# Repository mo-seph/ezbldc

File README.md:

# ezbldc

A four-channel driver board for small gimbal-type brushless motors: a
Seeed XIAO ESP32-S3 Plus, four TI DRV8313 three-phase drivers, four encoder
ports, I2C in and out on Qwiic connectors, one 12 V supply. 80 × 62 mm,
four layers, designed in KiCad 10 for assembly at JLCPCB.

## Status

Revision **v0.4**. The design passes KiCad's electrical and design rule
checks, the board matches the schematic, and the design and fabrication
files have been through three review rounds. **No test results on real
hardware are recorded here yet: treat it as an unproven design.** The
things most likely to need attention are under [Things to know](#things-to-know).

## What is on it

- **Four motor channels.** Each is a DRV8313 wired as TI's reference
  circuit, with its own 1.1 A-hold polyfuse, 100 µF bulk capacitor and a
  red fault LED. Phase traces are 0.65 mm (about 1.7 A for a 10 °C rise).
  Motors plug onto plain 1 × 3, 2.54 mm headers.
- **Three PWM inputs per channel** from the XIAO (twelve in all, which is
  exactly what the ESP32-S3's two motor-control PWM units provide). There
  is no current sensing: the board is driven in voltage mode.
- **One shared enable line** on the drivers' reset pins, pulled low, so
  the outputs are off through boot, reset and flashing, and a low pulse
  clears a latched fault.
- **Four encoder ports** (JST-XH, 5 pin) beside the motor headers: a
  shared clock and data line and one chip select each, from a 74HC139.
- **I2C** on two Qwiic connectors (in and out). Pull-ups are not fitted.
- **Power**: 12 V on a 5.5 mm barrel jack (2.0 mm pin), centre positive,
  with a second jack wired straight through for the next board. Reverse-polarity
  diode, 15 V TVS clamp, and a 7805 making 5 V for the XIAO.
- A WS2812B status LED and fourteen test pads.

## Pin map

| Function | XIAO pad | GPIO |
|---|---|---|
| Motor 1 IN1 / IN2 / IN3 | D9 / D17 / D10 | 8 / 13 / 9 |
| Motor 2 IN1 / IN2 / IN3 | D19 / D8 / D18 | 11 / 7 / 12 |
| Motor 3 IN1 / IN2 / IN3 | D12 / D2 / D13 | 39 / 3 / 40 |
| Motor 4 IN1 / IN2 / IN3 | D0 / D11 / D1 | 1 / 38 / 2 |
| Driver enable (high = on) | D3 | 4 |
| Encoder clock | D14 | 41 |
| Encoder data | D15 | 42 |
| Encoder select A0 / A1 | D6 / D7 | 43 / 44 |
| Status LED data | D16 | 10 |
| I2C SDA / SCL | D4 / D5 | 5 / 6 |

D11–D19 are the XIAO Plus's extra pads, the small ones between its
fourteen main edge pads. `kicad/design_spec.py` is the authority for this
table.

## Connectors

- **Motor headers J11–J14**: pin 1 (phase 1) is the one nearest the
  middle of the board, pin 3 is at the board edge.
- **Encoder sockets J21–J24**: pin 1 is at the board edge.
  1 = 3V3, 2 = GND, 3 = clock, 4 = data, 5 = chip select (active low).
  Select lines A1 A0 = 00, 01, 10, 11 pick encoder 1, 2, 3, 4. One select
  is always low.
- **Qwiic J3 (in), J4 (out)**: 1 = GND, 2 = 3V3, 3 = SDA, 4 = SCL. The 3V3
  wire only passes from one connector to the other; closing jumper JP1
  joins it to the board's own 3.3 V.
- **J1 / J2**: 12 V in and out, centre positive.

The board itself carries no part designators (it is too dense).
[`kicad/output/assembly_top.pdf`](kicad/output/assembly_top.pdf) is the map
of which part is where.

## Encoder options

The port was designed for MagnTek MT6701 encoders read over SSI. What it
supports:

- **No encoder**: run a channel open loop.
- **One MT6701 on SSI**: fine, in any socket.
- **Several MT6701 on SSI: unproven.** With its chip select high an
  MT6701 becomes an I2C slave on the same clock and data pins, and its
  datasheet does not say the data pin is released. It may well work at an
  SSI clock of about 1 MHz or less; it has not been tested. If it does
  not, a tri-state buffer in the data line at each encoder, enabled by
  that encoder's chip select, fixes it without changing this board.
- **Other SPI-type encoders**: any part whose data output goes
  high-impedance while its chip select is high, and which can be read
  without a MOSI line (the port has none).
- **I2C encoders on the same two pins**, as a firmware choice: data is
  SDA (it has a 10 k pull-up and 100 Ω in series), clock is SCL. The
  clock line has **no pull-up on this board**, so the encoder boards must
  bring one. Leave pin 5 unwired. The encoders need distinct addresses.

## Things to know

- **Sustained current.** The input diode D1 is the warmest part of the
  supply path. About 3 A for the whole board is the comfortable sustained
  figure; the jacks are rated 5 A.
- **7805 heat.** About 0.7 W with the XIAO's radio off, about 1.25 W with
  WiFi on, which wants a heatsink. A K7805-500R3 switching module fits
  the same three holes. The silkscreen shows which side the tab goes:
  fitted backwards, the regulator puts about 11 V on the XIAO's 5 V pin.
- **The XIAO is soldered on by hand**, flat on its pads. JLCPCB do not
  stock it.
- **The status LED runs from 3.3 V**, below that part's rated 3.5 V.
- **Fault outputs light LEDs only.** The microcontroller cannot read
  them: all its pins are used.
- **Ten logic nets are autorouted.** They pass the rule checks but are
  not tidy. Power, the motor phases, the buses and the I2C lines are
  routed by hand (in `kicad/tools/build_board.py`).
- SDA, SCL and the Qwiic 3V3 wire cross the board on inner layer 2,
  through the 3.3 V plane.

## What is in this repository

| Path | What |
|---|---|
| `kicad/bldc_driver_board.kicad_pro` | The KiCad 10 project: two-page schematic and the routed board |
| `kicad/lib/` | The custom symbols and footprints (XIAO Plus, barrel jack, regulator) and their generators |
| `kicad/output/schematic.pdf` | The schematic |
| `kicad/output/assembly_top.pdf` | Part positions, with pin 1 marked |
| `kicad/output/signal_map.png` | The copper, coloured by kind of signal |
| `kicad/output/bldc_driver_board.step` | 3D model |
| `kicad/output/fab/` | Gerbers and drill files (zipped and loose), JLCPCB placement file and BOMs |
| `BOM.md`, `bom_jlcpcb.csv` | Parts with LCSC numbers, and an assembly cost estimate |
| `kicad/design_spec.py` | Every part and net, as data. The schematic and board are generated from it |
| `kicad/gen_schematic.py`, `kicad/tools/` | The generators (see below) |

## Ordering from JLCPCB

1. Upload `kicad/output/fab/bldc_driver_board_gerbers.zip`. It should be
   detected as 4 layers, 80 × 62.05 mm. Inner layer 1 is the solid ground
   plane.
2. Choose a lead-free HASL or ENIG finish rather than the default OSP:
   the XIAO and any hand-fitted parts are soldered after the board has
   been through the oven. State the layer order in the remark field:
   F_Cu, In1_Cu (`.g1`), In2_Cu (`.g2`), B_Cu.
3. Assembly: top side. Upload `bom_jlcpcb.csv` (or
   `bom_jlcpcb_smd_only.csv` to fit the through-hole parts yourself) and
   `cpl_jlcpcb.csv`.
4. **Check the placement preview** against `assembly_top.pdf` before
   paying: the + of the five round capacitors, pin 1 of the five ICs, the
   cathode stripe of the three diodes and four fault LEDs, the status LED,
   and that the Qwiic sockets face outward. The rotations in the
   placement file were worked out part by part from JLCPCB's own
   footprints, but their preview is the final word.

## Regenerating the design

The schematic and the board are generated, not drawn:

- `python3 kicad/gen_schematic.py` writes the schematic from
  `design_spec.py` (`check` runs ERC and compares the netlist with the
  spec; `export` writes the PDF).
- `kicad/tools/build_board.py`, run with KiCad's own Python, builds the
  board: placement, all hand-designed copper, planes, silkscreen.
- `kicad/tools/autoroute.py` has Freerouting place the remaining logic
  nets and runs the design rule check.
- `kicad/tools/export_outputs.py` rewrites everything in `kicad/output/`.

**`build_board.py` and `autoroute.py` overwrite the board file.** Anything
edited by hand in KiCad is lost if they are run again, and the autorouter
gives a different result each time.

They were written for KiCad 10 on macOS and have paths to match. The
autorouter step also needs Freerouting 2.1.0 (Java 21) and, for the
Specctra export and import, a local install of the KiCad MCP server that
`kicad/tools/kicad_cmd.py` calls; adapt that file to your own setup.
`export_outputs.py` needs `rsvg-convert`.

A few comments and schematic notes mention a "Node" board and a
"Central". These are other boards in the system this one was built for:
an earlier I2C peripheral board whose outline, mounting holes and
connector positions this board copies, and the I2C bus controller.

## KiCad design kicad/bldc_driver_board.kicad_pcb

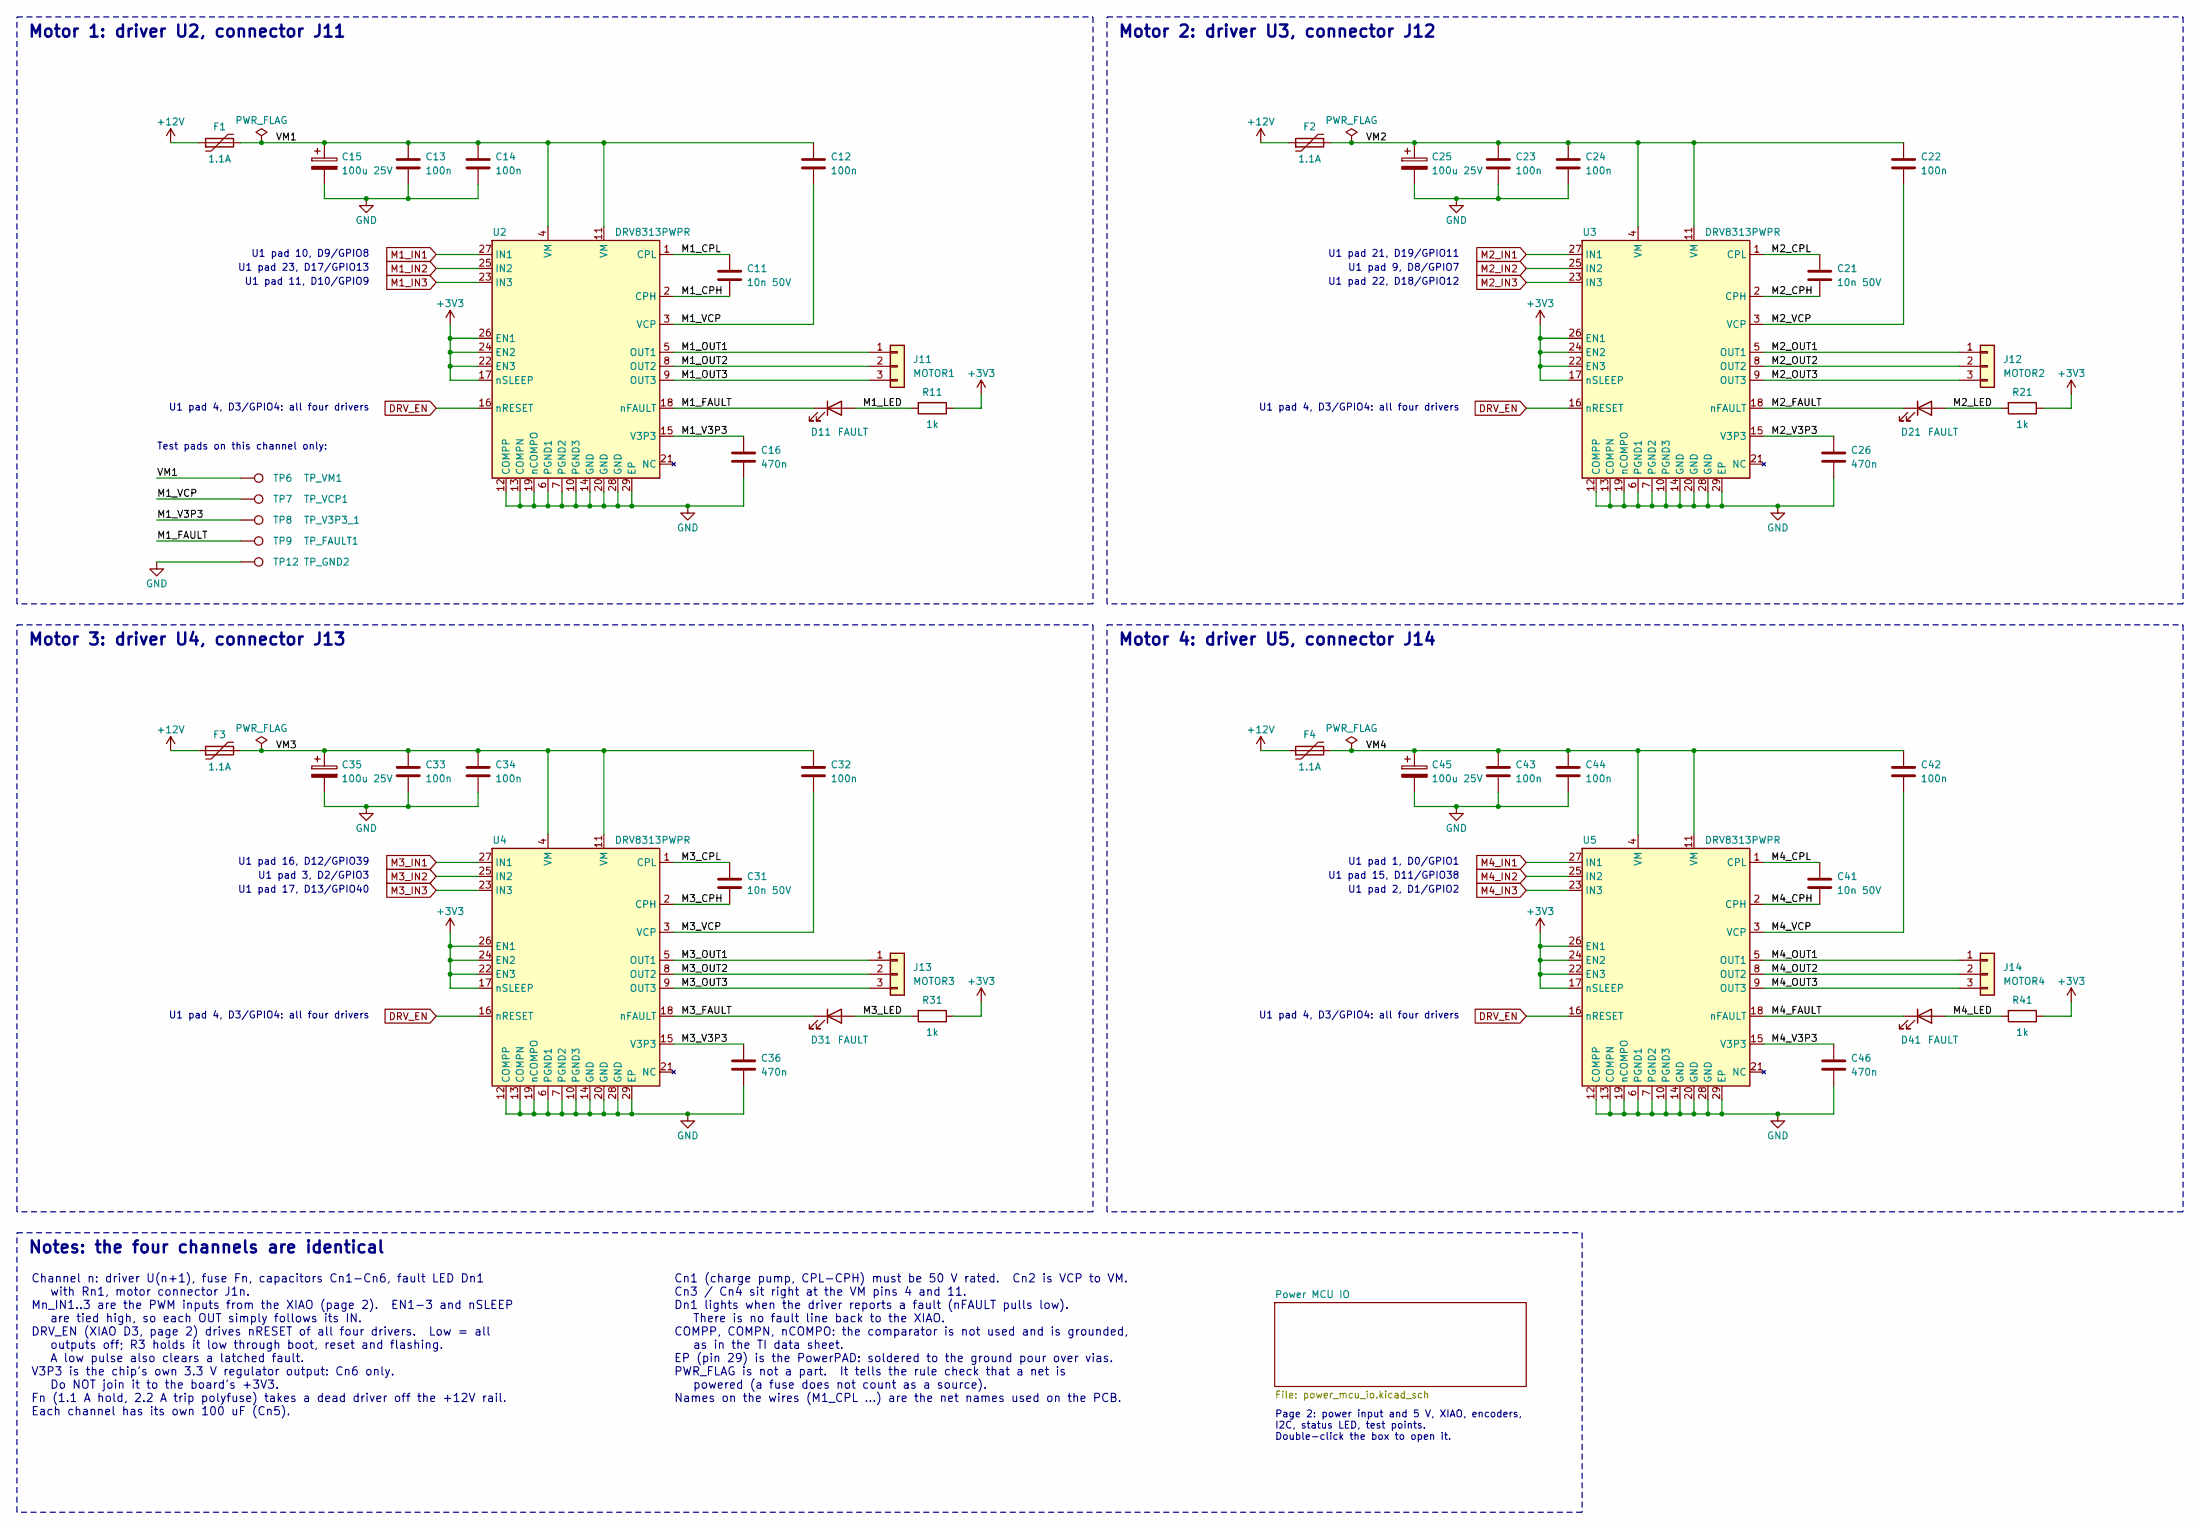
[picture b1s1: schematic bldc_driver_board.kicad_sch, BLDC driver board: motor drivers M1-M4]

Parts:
C11, C21, C31, C41: 10n 50V; C_0805_2012Metric; LCSC C1710
C12, C13, C14, C22, C23, C24, C32, C33, C34, C42, C43, C44: 100n; C_0805_2012Metric; LCSC C49678
C15, C25, C35, C45: 100u 25V; CP_Elec_6.3x7.7; LCSC C2836443
C16, C26, C36, C46: 470n; C_0805_2012Metric; LCSC C13967
D11, D21, D31, D41: FAULT; LED_0805_2012Metric; LCSC C84256
F1, F2, F3, F4: 1.1A; Fuse_1812_4532Metric; LCSC C21000
J11: MOTOR1; PinHeader_1x03_P2.54mm_Vertical; LCSC C2937625
J12: MOTOR2; PinHeader_1x03_P2.54mm_Vertical; LCSC C2937625
J13: MOTOR3; PinHeader_1x03_P2.54mm_Vertical; LCSC C2937625
J14: MOTOR4; PinHeader_1x03_P2.54mm_Vertical; LCSC C2937625
R11, R21, R31, R41: 1k; R_0805_2012Metric; LCSC C17513
TP6: TP_VM1; TestPoint_Pad_D1.5mm
TP7: TP_VCP1; TestPoint_Pad_D1.5mm
TP8: TP_V3P3_1; TestPoint_Pad_D1.5mm
TP9: TP_FAULT1; TestPoint_Pad_D1.5mm
TP12: TP_GND2; TestPoint_Pad_D1.5mm
U2, U3, U4, U5: DRV8313PWPR; HTSSOP-28-1EP_4.4x9.7mm_P0.65mm_EP2.85x5.4mm_ThermalVias; LCSC C92482

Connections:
+3V3: R11.1, R21.1, R31.1, R41.1, U2.17 (nSLEEP), U2.22 (EN3), U2.24 (EN2), U2.26 (EN1), U3.17 (nSLEEP), U3.22 (EN3), U3.24 (EN2), U3.26 (EN1), U4.17 (nSLEEP), U4.22 (EN3), U4.24 (EN2), U4.26 (EN1), U5.17 (nSLEEP), U5.22 (EN3), U5.24 (EN2), U5.26 (EN1); also elsewhere on the board
+12V: F1.1, F2.1, F3.1, F4.1; also elsewhere on the board
/M1_CPH: C11.2, U2.2 (CPH)
/M1_CPL: C11.1, U2.1 (CPL)
/M1_FAULT: D11.1 (K), TP9.1, U2.18 (nFAULT)
/M1_LED: D11.2 (A), R11.2
/M1_OUT1: J11.1, U2.5 (OUT1)
/M1_OUT2: J11.2, U2.8 (OUT2)
/M1_OUT3: J11.3, U2.9 (OUT3)
/M1_V3P3: C16.1, TP8.1, U2.15 (V3P3)
/M1_VCP: C12.1, TP7.1, U2.3 (VCP)
/M2_CPH: C21.2, U3.2 (CPH)
/M2_CPL: C21.1, U3.1 (CPL)
/M2_FAULT: D21.1 (K), U3.18 (nFAULT)
/M2_LED: D21.2 (A), R21.2
/M2_OUT1: J12.1, U3.5 (OUT1)
/M2_OUT2: J12.2, U3.8 (OUT2)
/M2_OUT3: J12.3, U3.9 (OUT3)
/M2_V3P3: C26.1, U3.15 (V3P3)
/M2_VCP: C22.1, U3.3 (VCP)
/M3_CPH: C31.2, U4.2 (CPH)
/M3_CPL: C31.1, U4.1 (CPL)
/M3_FAULT: D31.1 (K), U4.18 (nFAULT)
/M3_LED: D31.2 (A), R31.2
/M3_OUT1: J13.1, U4.5 (OUT1)
/M3_OUT2: J13.2, U4.8 (OUT2)
/M3_OUT3: J13.3, U4.9 (OUT3)
/M3_V3P3: C36.1, U4.15 (V3P3)
/M3_VCP: C32.1, U4.3 (VCP)
/M4_CPH: C41.2, U5.2 (CPH)
/M4_CPL: C41.1, U5.1 (CPL)
/M4_FAULT: D41.1 (K), U5.18 (nFAULT)
/M4_LED: D41.2 (A), R41.2
/M4_OUT1: J14.1, U5.5 (OUT1)
/M4_OUT2: J14.2, U5.8 (OUT2)
/M4_OUT3: J14.3, U5.9 (OUT3)
/M4_V3P3: C46.1, U5.15 (V3P3)
/M4_VCP: C42.1, U5.3 (VCP)
/VM1: C12.2, C13.1, C14.1, C15.1, F1.2, TP6.1, U2.4 (VM), U2.11 (VM)
/VM2: C22.2, C23.1, C24.1, C25.1, F2.2, U3.4 (VM), U3.11 (VM)
/VM3: C32.2, C33.1, C34.1, C35.1, F3.2, U4.4 (VM), U4.11 (VM)
/VM4: C42.2, C43.1, C44.1, C45.1, F4.2, U5.4 (VM), U5.11 (VM)
DRV_EN: U2.16 (nRESET), U3.16 (nRESET), U4.16 (nRESET), U5.16 (nRESET); also elsewhere on the board
GND: C13.2, C14.2, C15.2, C16.2, C23.2, C24.2, C25.2, C26.2, C33.2, C34.2, C35.2, C36.2, C43.2, C44.2, C45.2, C46.2, TP12.1, U2.6 (PGND1), U2.7 (PGND2), U2.10 (PGND3), U2.12 (COMPP), U2.13 (COMPN), U2.14 (GND), U2.19 (nCOMPO), U2.20 (GND), U2.28 (GND), U2.29 (EP), U3.6 (PGND1), U3.7 (PGND2), U3.10 (PGND3), U3.12 (COMPP), U3.13 (COMPN), U3.14 (GND), U3.19 (nCOMPO), U3.20 (GND), U3.28 (GND), U3.29 (EP), U4.6 (PGND1), U4.7 (PGND2), U4.10 (PGND3), U4.12 (COMPP), U4.13 (COMPN), U4.14 (GND), U4.19 (nCOMPO), U4.20 (GND), U4.28 (GND), U4.29 (EP), U5.6 (PGND1), U5.7 (PGND2), U5.10 (PGND3), U5.12 (COMPP), U5.13 (COMPN), U5.14 (GND), U5.19 (nCOMPO), U5.20 (GND), U5.28 (GND), U5.29 (EP); also elsewhere on the board
M1_IN1: U2.27 (IN1); also elsewhere on the board
M1_IN2: U2.25 (IN2); also elsewhere on the board
M1_IN3: U2.23 (IN3); also elsewhere on the board
M2_IN1: U3.27 (IN1); also elsewhere on the board
M2_IN2: U3.25 (IN2); also elsewhere on the board
M2_IN3: U3.23 (IN3); also elsewhere on the board
M3_IN1: U4.27 (IN1); also elsewhere on the board
M3_IN2: U4.25 (IN2); also elsewhere on the board
M3_IN3: U4.23 (IN3); also elsewhere on the board
M4_IN1: U5.27 (IN1); also elsewhere on the board
M4_IN2: U5.25 (IN2); also elsewhere on the board
M4_IN3: U5.23 (IN3); also elsewhere on the board

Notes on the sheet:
Motor 1: driver U2, connector J11
U1 pad 10, D9/GPIO8
U1 pad 23, D17/GPIO13
U1 pad 11, D10/GPIO9
U1 pad 4, D3/GPIO4: all four drivers
Test pads on this channel only:
Motor 2: driver U3, connector J12
U1 pad 21, D19/GPIO11
U1 pad 9, D8/GPIO7
U1 pad 22, D18/GPIO12
Motor 3: driver U4, connector J13
U1 pad 16, D12/GPIO39
U1 pad 3, D2/GPIO3
U1 pad 17, D13/GPIO40
Motor 4: driver U5, connector J14
U1 pad 1, D0/GPIO1
U1 pad 15, D11/GPIO38
U1 pad 2, D1/GPIO2
Notes: the four channels are identical
Channel n: driver U(n+1), fuse Fn, capacitors Cn1-Cn6, fault LED Dn1 with Rn1, motor connector J1n. Mn_IN1..3 are the PWM inputs from the XIAO (page 2). EN1-3 and nSLEEP are tied high, so each OUT simply follows its IN. DRV_EN (XIAO D3, page 2) drives nRESET of all four drivers. Low = all outputs o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
Cn1 (charge pump, CPL-CPH) must be 50 V rated. Cn2 is VCP to VM. Cn3 / Cn4 sit right at the VM pins 4 and 11. Dn1 lights when the driver reports a fault (nFAULT pulls low). There is no fault line back to the XIAO. COMPP, COMPN, nCOMPO: the comparator is not used and is grounded, as in the TI data s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
Page 2: power input and 5 V, XIAO, encoders, I2C, status LED, test points. Double-click the box to open it.

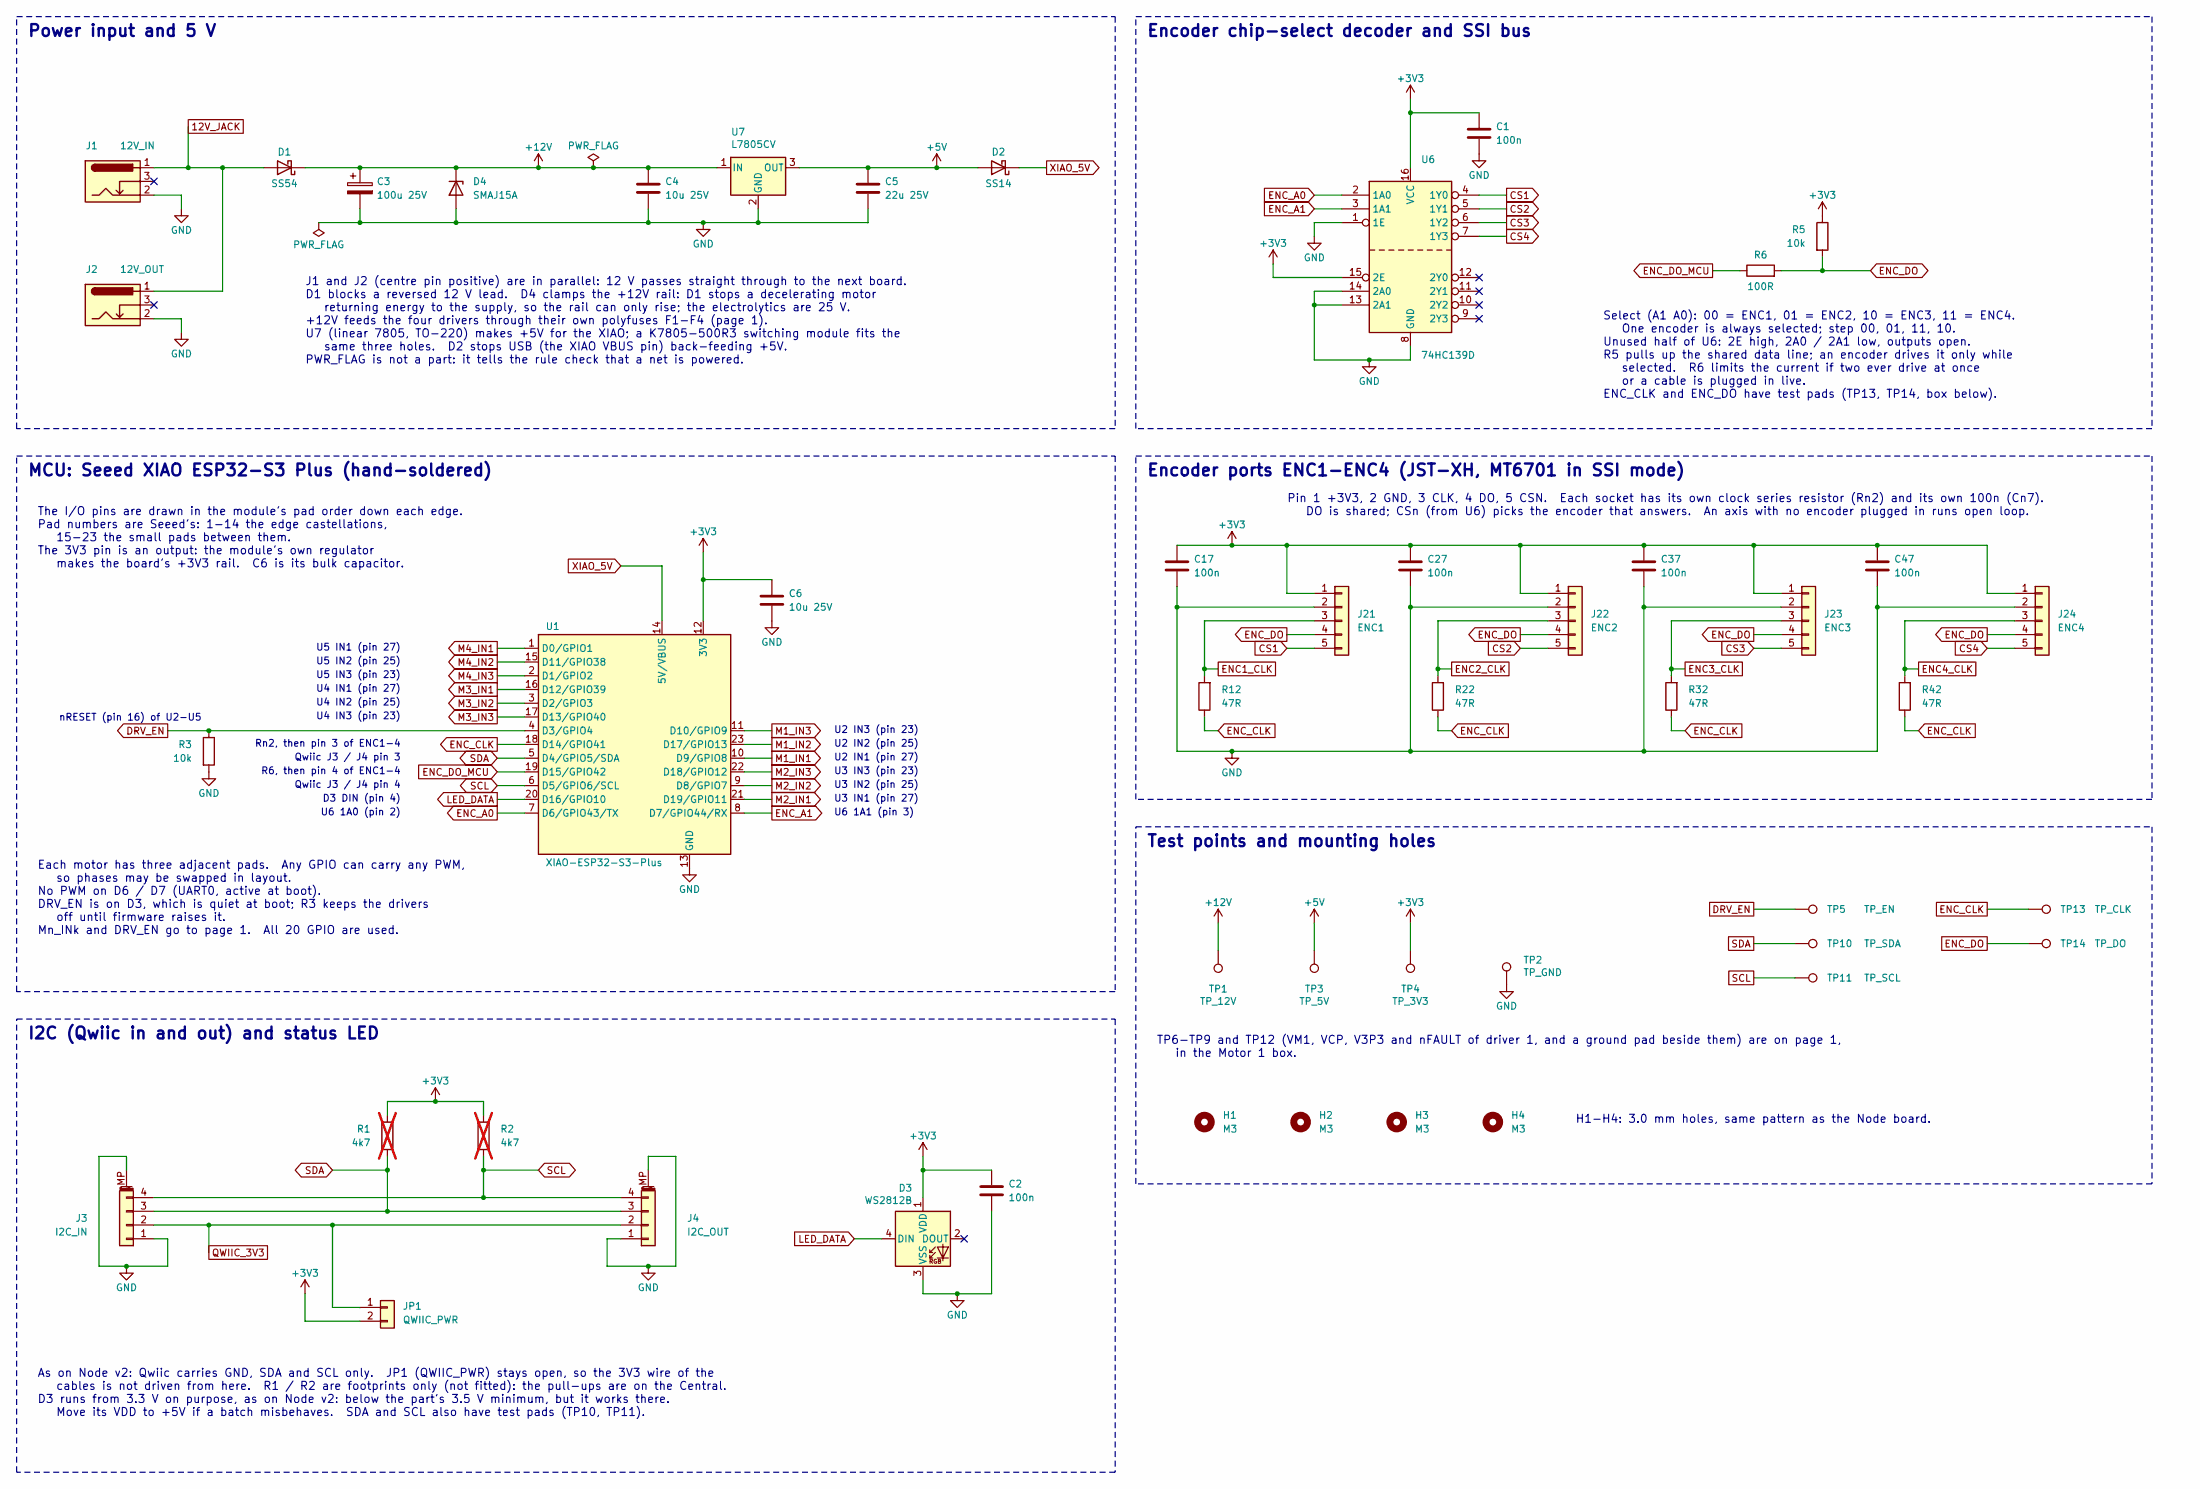
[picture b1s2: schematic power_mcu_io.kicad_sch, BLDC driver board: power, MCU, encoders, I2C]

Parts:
C1, C2: 100n; C_0805_2012Metric; LCSC C49678
C3: 100u 25V; CP_Elec_6.3x7.7; LCSC C2836443
C4, C6: 10u 25V; C_0805_2012Metric; LCSC C15850
C5: 22u 25V; C_0805_2012Metric; LCSC C45783
C17, C27, C37, C47: 100n; C_0603_1608Metric; LCSC C14663
D1: SS54; D_SMA; LCSC C22452
D2: SS14; D_SMA; LCSC C2480
D3: WS2812B; LED_WS2812B_PLCC4_5.0x5.0mm_P3.2mm; LCSC C2843785
D4: SMAJ15A; D_SMA; LCSC C86819
H1, H2, H3, H4: M3; MountingHole_3mm
J1: 12V_IN; XKB_DC-005-5A-2.0; LCSC C381116
J2: 12V_OUT; XKB_DC-005-5A-2.0; LCSC C381116
J3: I2C_IN; JST_SH_SM04B-SRSS-TB_1x04-1MP_P1.00mm_Horizontal; LCSC C160404
J4: I2C_OUT; JST_SH_SM04B-SRSS-TB_1x04-1MP_P1.00mm_Horizontal; LCSC C160404
J21: ENC1; JST_XH_B5B-XH-A_1x05_P2.50mm_Vertical; LCSC C157991
J22: ENC2; JST_XH_B5B-XH-A_1x05_P2.50mm_Vertical; LCSC C157991
J23: ENC3; JST_XH_B5B-XH-A_1x05_P2.50mm_Vertical; LCSC C157991
J24: ENC4; JST_XH_B5B-XH-A_1x05_P2.50mm_Vertical; LCSC C157991
JP1: QWIIC_PWR; PinHeader_1x02_P2.54mm_Vertical; LCSC C492401
R1, R2: 4k7; R_0805_2012Metric; LCSC C17673; not fitted
R3, R5: 10k; R_0805_2012Metric; LCSC C17414
R6: 100R; R_0805_2012Metric; LCSC C17408
R12, R22, R32, R42: 47R; R_0603_1608Metric; LCSC C23182
TP1: TP_12V; TestPoint_Pad_D1.5mm
TP2: TP_GND; TestPoint_Pad_D1.5mm
TP3: TP_5V; TestPoint_Pad_D1.5mm
TP4: TP_3V3; TestPoint_Pad_D1.5mm
TP5: TP_EN; TestPoint_Pad_D1.5mm
TP10: TP_SDA; TestPoint_Pad_D1.5mm
TP11: TP_SCL; TestPoint_Pad_D1.5mm
TP13: TP_CLK; TestPoint_Pad_D1.5mm
TP14: TP_DO; TestPoint_Pad_D1.5mm
U1: XIAO-ESP32-S3-Plus; XIAO-ESP32-S3-Plus-SMD
U6: 74HC139D; SOIC-16_3.9x9.9mm_P1.27mm; LCSC C5603
U7: L7805CV; SIP-3_K7805_or_TO-220; LCSC C111887

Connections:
12V_JACK: D1.2 (A), J1.1, J2.1
+3V3: C1.1, C2.1, C6.1, C17.1, C27.1, C37.1, C47.1, D3.1 (VDD), J21.1, J22.1, J23.1, J24.1, JP1.2, R1.1, R2.1, R5.1, TP4.1, U1.12 (3V3), U6.15 (2E), U6.16 (VCC); also elsewhere on the board
+5V: C5.1, D2.2 (A), TP3.1, U7.3 (OUT)
+12V: C3.1, C4.1, D1.1 (K), D4.1 (K), TP1.1, U7.1 (IN); also elsewhere on the board
CS1: J21.5, U6.4 (1Y0)
CS2: J22.5, U6.5 (1Y1)
CS3: J23.5, U6.6 (1Y2)
CS4: J24.5, U6.7 (1Y3)
DRV_EN: R3.1, TP5.1, U1.4 (D3/GPIO4); also elsewhere on the board
ENC1_CLK: J21.3, R12.2
ENC2_CLK: J22.3, R22.2
ENC3_CLK: J23.3, R32.2
ENC4_CLK: J24.3, R42.2
ENC_A0: U1.7 (D6/GPIO43/TX), U6.2 (1A0)
ENC_A1: U1.8 (D7/GPIO44/RX), U6.3 (1A1)
ENC_CLK: R12.1, R22.1, R32.1, R42.1, TP13.1, U1.18 (D14/GPIO41)
ENC_DO: J21.4, J22.4, J23.4, J24.4, R5.2, R6.2, TP14.1
ENC_DO_MCU: R6.1, U1.19 (D15/GPIO42)
GND: C1.2, C2.2, C3.2, C4.2, C5.2, C6.2, C17.2, C27.2, C37.2, C47.2, D3.3 (VSS), D4.2 (A), J1.2, J2.2, J3.1, J3.MP (MountPin), J4.1, J4.MP (MountPin), J21.2, J22.2, J23.2, J24.2, R3.2, TP2.1, U1.13 (GND), U6.1 (1E), U6.8 (GND), U6.13 (2A1), U6.14 (2A0), U7.2 (GND); also elsewhere on the board
LED_DATA: D3.4 (DIN), U1.20 (D16/GPIO10)
M1_IN1: U1.10 (D9/GPIO8); also elsewhere on the board
M1_IN2: U1.23 (D17/GPIO13); also elsewhere on the board
M1_IN3: U1.11 (D10/GPIO9); also elsewhere on the board
M2_IN1: U1.21 (D19/GPIO11); also elsewhere on the board
M2_IN2: U1.9 (D8/GPIO7); also elsewhere on the board
M2_IN3: U1.22 (D18/GPIO12); also elsewhere on the board
M3_IN1: U1.16 (D12/GPIO39); also elsewhere on the board
M3_IN2: U1.3 (D2/GPIO3); also elsewhere on the board
M3_IN3: U1.17 (D13/GPIO40); also elsewhere on the board
M4_IN1: U1.1 (D0/GPIO1); also elsewhere on the board
M4_IN2: U1.15 (D11/GPIO38); also elsewhere on the board
M4_IN3: U1.2 (D1/GPIO2); also elsewhere on the board
QWIIC_3V3: J3.2, J4.2, JP1.1
SCL: J3.4, J4.4, R2.2, TP11.1, U1.6 (D5/GPIO6/SCL)
SDA: J3.3, J4.3, R1.2, TP10.1, U1.5 (D4/GPIO5/SDA)
XIAO_5V: D2.1 (K), U1.14 (5V/VBUS)

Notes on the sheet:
Power input and 5 V
J1 and J2 (centre pin positive) are in parallel: 12 V passes straight through to the next board. D1 blocks a reversed 12 V lead. D4 clamps the +12V rail: D1 stops a decelerating motor returning energy to the supply, so the rail can only rise; the electrolytics are 25 V. +12V feeds the four drivers 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
MCU: Seeed XIAO ESP32-S3 Plus (hand-soldered)
U5 IN1 (pin 27)
U5 IN2 (pin 25)
U5 IN3 (pin 23)
U4 IN1 (pin 27)
U4 IN2 (pin 25)
U4 IN3 (pin 23)
Rn2, then pin 3 of ENC1-4
Qwiic J3 / J4 pin 3
R6, then pin 4 of ENC1-4
Qwiic J3 / J4 pin 4
D3 DIN (pin 4)
U6 1A0 (pin 2)
U2 IN3 (pin 23)
U2 IN2 (pin 25)
U2 IN1 (pin 27)
U3 IN3 (pin 23)
U3 IN2 (pin 25)
U3 IN1 (pin 27)
U6 1A1 (pin 3)
nRESET (pin 16) of U2-U5
The I/O pins are drawn in the module's pad order down each edge. Pad numbers are Seeed's: 1-14 the edge castellations, 15-23 the small pads between them. The 3V3 pin is an output: the module's own regulator makes the board's +3V3 rail. C6 is its bulk capacitor.
Each motor has three adjacent pads. Any GPIO can carry any PWM, so phases may be swapped in layout. No PWM on D6 / D7 (UART0, active at boot). DRV_EN is on D3, which is quiet at boot; R3 keeps the drivers off until firmware raises it. Mn_INk and DRV_EN go to page 1. All 20 GPIO are used.
I2C (Qwiic in and out) and status LED
As on Node v2: Qwiic carries GND, SDA and SCL only. JP1 (QWIIC_PWR) stays open, so the 3V3 wire of the cables is not driven from here. R1 / R2 are footprints only (not fitted): the pull-ups are on the Central. D3 runs from 3.3 V on purpose, as on Node v2: below the part's 3.5 V minimum, but it work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
Encoder chip-select decoder and SSI bus
Select (A1 A0): 00 = ENC1, 01 = ENC2, 10 = ENC3, 11 = ENC4. One encoder is always selected; step 00, 01, 11, 10. Unused half of U6: 2E high, 2A0 / 2A1 low, outputs open. R5 pulls up the shared data line; an encoder drives it only while selected. R6 limits the current if two ever drive at once or a 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
Encoder ports ENC1-ENC4 (JST-XH, MT6701 in SSI mode)
Pin 1 +3V3, 2 GND, 3 CLK, 4 DO, 5 CSN. Each socket has its own clock series resistor (Rn2) and its own 100n (Cn7). DO is shared; CSn (from U6) picks the encoder that answers. An axis with no encoder plugged in runs open loop.
Test points and mounting holes
TP6-TP9 and TP12 (VM1, VCP, V3P3 and nFAULT of driver 1, and a ground pad beside them) are on page 1, in the Motor 1 box.
H1-H4: 3.0 mm holes, same pattern as the Node board.

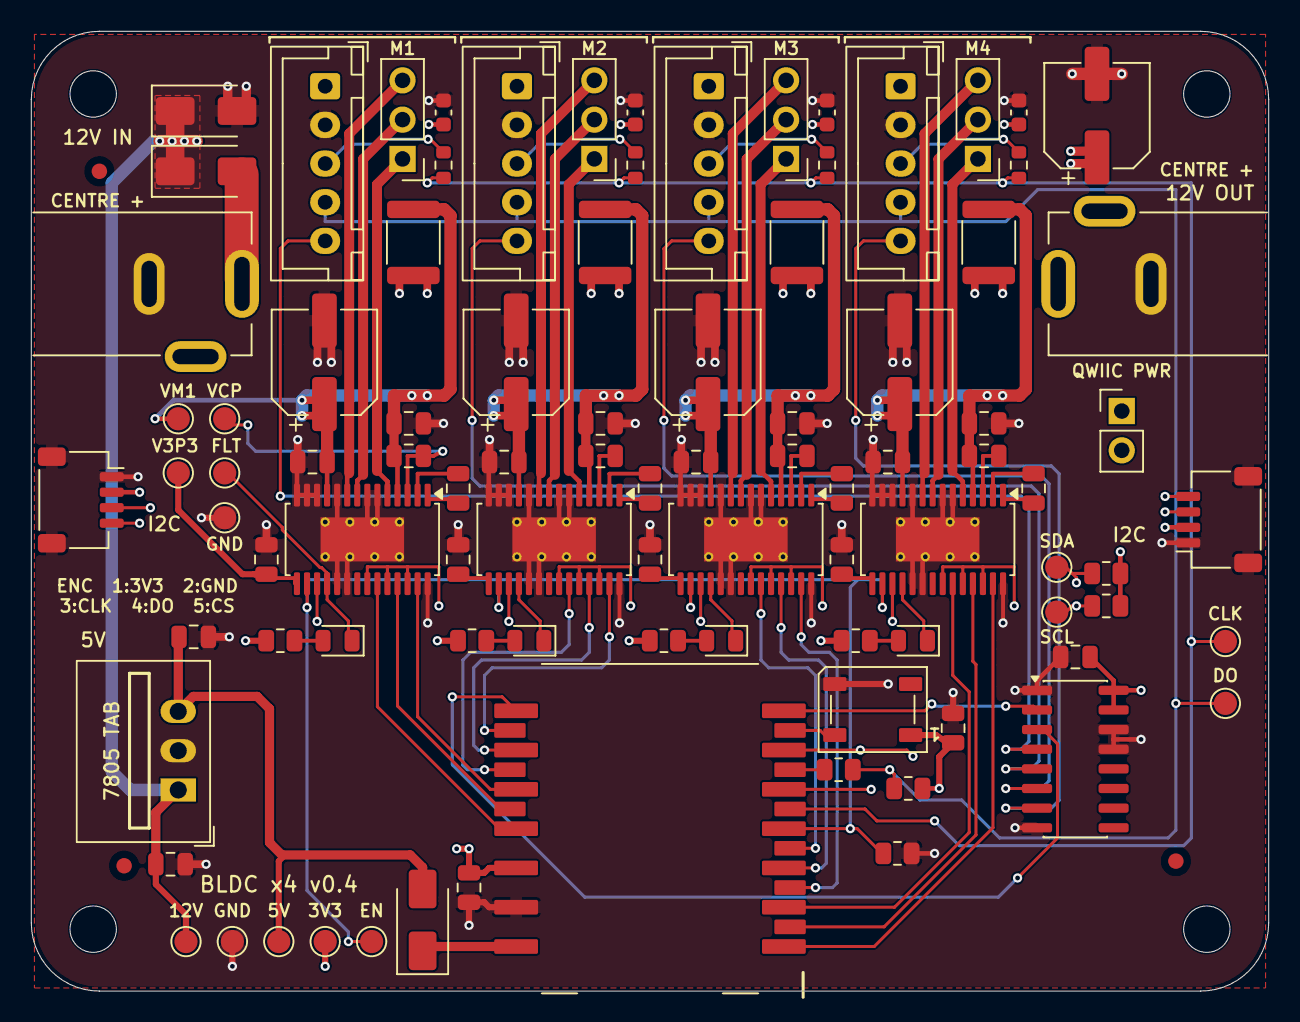
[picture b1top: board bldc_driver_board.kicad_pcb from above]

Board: 4 copper layers, 80.0 x 62.1 mm, 100 parts (0 on the bottom side), 76 nets.

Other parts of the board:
FID1, FID2, FID3: Fiducial; Fiducial_1mm_Mask2mm

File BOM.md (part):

# 4-channel BLDC driver board — BOM (per board)

Parts were checked against JLCPCB's live catalogue on 2026-11-10 and
2026-11-11 (part number, package, basic / extended, stock). Prices are
JLCPCB's quantity-1 tier in USD on those days. `bom_jlcpcb.csv` is the
same list in JLCPCB's upload format;
`kicad/output/fab/bom_jlcpcb_smd_only.csv` is the surface-mount half, for
an order where the through-hole parts are fitted by hand. Designators
match the KiCad project.

## Surface mount (JLCPCB assembles these)

| Designators | Qty | Part | Package | LCSC | JLCPCB | $ each |
|---|---|---|---|---|---|---|
| U2, U3, U4, U5 | 4 | DRV8313PWPR (TI) | HTSSOP-28, PowerPAD | C92482 | extended | 4.47 |
| U6 | 1 | 74HC139D,653 (Nexperia) | SOIC-16 | C5603 | extended | 0.25 |
| C12 C13 C14, C22 C23 C24, C32 C33 C34, C42 C43 C44, C1, C2 | 14 | 100 nF 50 V X7R | 0805 | C49678 | basic | 0.015 |
| C11, C21, C31, C41 | 4 | 10 nF 50 V X7R | 0805 | C1710 | basic | 0.010 |
| C16, C26, C36, C46 | 4 | 470 nF 50 V X7R | 0805 | C13967 | basic | 0.019 |
| C15, C25, C35, C45, C3 | 5 | 100 µF 25 V aluminium, Ø6.3 × 7.7 mm | SMD can | C2836443 | extended | 0.04 |
| C4, C6 | 2 | 10 µF 25 V X5R (C6 is the bulk capacitor on +3V3 at the XIAO) | 0805 | C15850 | basic | 0.035 |
| D4 | 1 | SMAJ15A/TR13 (Brightking), 15 V unidirectional TVS, clamps the 12 V rail | SMA | C86819 | extended | 0.048 |
| C5 | 1 | 22 µF 25 V X5R | 0805 | C45783 | basic | 0.11 |
| R11, R21, R31, R41 | 4 | 1 kΩ 1 % | 0805 | C17513 | basic | 0.004 |
| R3, R5 | 2 | 10 kΩ 1 % | 0805 | C17414 | basic | 0.003 |
| R6 | 1 | 100 Ω 1 % (encoder data line, in series at the XIAO) | 0805 | C17408 | basic | 0.004 |
| R12, R22, R32, R42 | 4 | 47 Ω 1 % (encoder clock, one in series at each socket) | 0603 | C23182 | basic | 0.002 |
| C17, C27, C37, C47 | 4 | 100 nF 50 V X7R (3V3 decoupling at each encoder socket) | 0603 | C14663 | basic | 0.006 |
| F1, F2, F3, F4 | 4 | Polyfuse 1.1 A hold, 2.2 A trip, 33 V (SMD1812P110TF/33). 2 A hold / 24 V (SMD1812P200TF/24, C434887, $0.20) fits the same pads | 1812 | C21000 | extended | 0.147 |
| D11, D21, D31, D41 | 4 | LED red (NCD0805R1) | 0805 | C84256 | basic | 0.013 |
| D1 | 1 | SS54 Schottky 5 A 40 V | SMA | C22452 | basic | 0.045 |
| D2 | 1 | SS14 Schottky 1 A 40 V | SMA | C2480 | basic | 0.019 |
| D3 | 1 | WS2812B (XL-5050RGBC-2812B) | 5050 | C2843785 | extended | 0.055 |
| J3, J4 | 2 | JST SM04B-SRSS-TB (Qwiic) | SMD, right angle | C160404 | extended | 0.21 |

Not fitted: R1, R2 (4.7 kΩ, 0805, C17673, basic). The I2C pull-ups are
expected on the bus controller; fit these if the board is used alone.

No part: fourteen test pads TP1–TP14 (bare 1.5 mm copper pads), three
fiducials, four mounting holes.

## Through-hole and hand-fitted

| Designators | Qty | Part | LCSC | JLCPCB | $ each |
|---|---|---|---|---|---|
| J11–J14 (motors) | 4 | 1 × 3 pin header, 2.54 mm (XFCN PZ254V-11-03P). Gimbal motors usually come with a 2.54 mm socket | C2937625 | extended, through-hole | 0.02 |
| J21–J24 (encoders) | 4 | JST B5B-XH-A, 5-pin 2.5 mm | C157991 | extended, through-hole | 0.09 |
| J1, J2 (12 V in, 12 V out) | 2 | XKB DC-005-5A-2.0 barrel jack | C381116 | extended, through-hole | 0.26 |
| U7 | 1 | L7805CV (ST), linear 5 V regulator, TO-220, standing. Alternative: K7805-500R3 switching module (C2992390, $1.75), same holes, same pin order | C111887 | extended, through-hole | 0.31 |
| JP1 (Qwiic power jumper) | 1 | 1 × 2 pin header, 2.54 mm (XFCN PZ254V-11-02P) | C492401 | extended, through-hole | 0.02 |
| U1 | 1 | Seeed XIAO ESP32-S3 Plus | not stocked at JLCPCB | hand solder | ≈ 9 (not checked) |

## Totals

| | USD |
|---|---|
| Surface-mount parts | ≈ 20.12 (the four DRV8313 are 17.88 of it) |
| Through-hole parts | ≈ 1.29 |
| **Parts JLCPCB supplies and fits** | **≈ 21.41** |
| XIAO ESP32-S3 Plus (hand-fitted) | ≈ 9 (not checked) |
| **Parts per board** | **≈ 30.40** |

## JLCPCB assembly estimate (2026-11-11)

Two ways to order. Either way the XIAO is fitted by hand: JLCPCB do not
stock it.

| Who fits what | smallest order (5 boards made, 2 assembled) | 10 boards, all assembled |
|---|---|---|
| **Full**: JLCPCB fit everything except the XIAO | ≈ $108 | ≈ $295 |
| **Surface-mount only**: JLCPCB fit the SMD parts, the through-hole parts are fitted by hand | ≈ $85, plus ≈ $2.60 of through-hole parts | ≈ $256, plus ≈ $13 of through-hole parts |
| What surface-mount only saves, after buying those parts separately | ≈ $20 | ≈ $26 |

Before shipping and import tax. The bare-board price in these is
JLCPCB's own: read off their calculator on 2026-11-11 for 4 layers,
80 × 62.05 mm, 1.6 mm, green, lead-free HASL.

Surface-mount only leaves 12 parts and 43 joints a board to do by hand:
four 1 × 3 motor headers, four JST-XH encoder sockets, two barrel jacks,
the 7805 and the Qwiic-power jumper header. The XIAO is another 23 joints
either way.

How those totals are made up. Counts are from the KiCad project: 64
surface-mount placements (260 joints), 12 through-hole parts (43 joints),
29 part types of which 12 are extended (7 surface-mount, 5 through-hole).
Fees are JLCPCB's published Economic PCBA rates as read on 2026-11-10:
setup $8.18, stencil $1.53, hand-soldering labour $3.58 per order, $3.07
per extended part type per order, $0.0016 per surface-mount joint, $0.0164
per hand-soldered joint.

| | Full, smallest order | Full, 10 boards | SMD only, smallest order | SMD only, 10 boards |
|---|---|---|---|---|
| Setup and stencil | 9.71 | 9.71 | 9.71 | 9.71 |
| Hand-solder labour | 3.58 | 3.58 | – | – |
| Extended part fee ($3.07 a type) | 36.84 (12 types) | 36.84 | 21.49 (7 types) | 21.49 |
| Joints | 2.24 ($1.12 a board) | 11.21 | 0.83 ($0.42 a board) | 4.16 |
| Components | 42.82 ($21.41 a board) | 214.10 | 40.24 ($20.12 a board) | 201.20 |
| Bare 4-layer boards, lead-free HASL (5 or 10 made) | 13.10 | 19.30 | 13.10 | 19.30 |
| **JLCPCB total before shipping and tax** | **≈ $108** | **≈ $295** | **≈ $85** | **≈ $256** |
| Through-hole parts bought separately ($1.29 a board) | – | – | ≈ 2.60 | ≈ 13 |
| Per working board, with those parts and a XIAO | ≈ $63 | ≈ $38 | ≈ $53 | ≈ $36 |

- There is no one-board order: the minimum is 5 bare boards with 2 of them
  assembled.
- Bare-board price by finish, five boards: $8.00 OSP (the page's
  default), $13.10 lead-free HASL, $25.20 ENIG. Ten boards: $14.00 OSP,
  $19.30 lead-free HASL. The table uses lead-free HASL: OSP solders
  poorly once it has been through the oven and sat for a while, and the
  XIAO and (in the surface-mount-only case) the through-hole parts are
  soldered afterwards. Vias: "Plugged" is the default for four layers
  and costs nothing ("Tented" is not offered).
- The assembly lines are computed from JLCPCB's published fees, not from
  a quote: their page gives assembly prices only after the files are
  uploaded.
- Component prices are quantity-1 tiers; at 10 boards the DRV8313 (40
  pieces) may drop a tier. JLCPCB also charges for a few spare passives.
- The $1.29 for through-hole parts is JLCPCB's own price for them.
- If any part turns out to be "Standard PCBA only", the fees change to
  setup $25.56, stencil $8.21 and $1.53 per part type: about $60 more per
  order.

## Notes

- **DRV8313 price.** JLCPCB charges $4.47 for a part LCSC lists at about
  $1.70. That makes a driver channel about $5 with its passives.
- **Polyfuse size.** 1.1 A hold, 2.2 A trip per channel. Four of them
  hold 4.4 A, which stays inside the 5 A rating of the jacks and of D1,
  so the fuses still protect the board's own input. A 2 A hold part
  (SMD1812P200TF/24, C434887) fits the same pads and would let one driver
  run at its full rating, but four of those hold 8 A, more than the input
  can carry: then only the supply's own limit protects the jack and D1.
  Polyfuses lose about a third of their hold current at 60 °C.
- **Sustained power.** D1 is the warmest part of the input: about 1 W at
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
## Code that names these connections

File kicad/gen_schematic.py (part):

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plain (local) label only on the root sheet; inside a sub-sheet the name gets
the sheet's name in front of it and would no longer match design_spec.py.
The driver channels have many nets that need a name but go nowhere else
(M1_CPL, M1_VCP ...), so they sit on the root where a plain label is enough.
Everything on page 2 is named by a global label or a power symbol.

The three custom symbols come from lib/bldc.kicad_sym (lib/gen_symbols.py),
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    sh.power('+3V3', X - 18, Y - 4)
    x, y = u.p(16)
    sh.wire((x, y), (x - 6, y))
    sh.glabel('DRV_EN', x - 6, y, 180, 'input')
    sh.hint('U1 pad 4, D3/GPIO4: all four drivers', x - 15.5, y, 'right')
    return X, Y


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    sh.wire(u7.p(3), d2.p(2))
    sh.power('+5V', ox + 134, rail)
    sh.wire(d2.p(1), (ox + 150, rail))
    sh.glabel('XIAO_5V', ox + 150, rail, 0, 'output')
    bar = rail + 8
    for part, pin in ((c3, 2), (d4, 2), (c4, 2), (u7, 2), (c5, 2)):
        sh.wire(part.p(pin), (part.p(pin)[0], bar))
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

MCU_HINTS = {
    'DRV_EN': 'nRESET (pin 16) of U2-U5',
    'ENC_CLK': 'Rn2, then pin 3 of ENC1-4',
    'ENC_DO_MCU': 'R6, then pin 4 of ENC1-4',
    'SDA': 'Qwiic J3 / J4 pin 3',
    'SCL': 'Qwiic J3 / J4 pin 4',
}
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    x, y = u.p(4)
    r3 = sh.part('R3', X - 62, y + 3, **LEFT)
    sh.wire((x, y), (X - 68, y))
    sh.glabel('DRV_EN', X - 68, y, 180, 'output')
    sh.hint(mcu_hint('DRV_EN'), X - 63, y - 1.8, 'right')
    sh.power('GND', *r3.p(2))
    # supply pins
    x, y = u.p(14)
    sh.wire((x, y), (x, y - 8), (x - 6, y - 8))
    sh.glabel('XIAO_5V', x - 6, y - 8, 180, 'input')
    x, y = u.p(12)
    sh.wire((x, y), (x, y - 10))
    sh.power('+3V3', x, y - 10)
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        'No PWM on D6 / D7 (UART0, active at boot).',
        'DRV_EN is on D3, which is quiet at boot; R3 keeps the drivers',
        '   off until firmware raises it.',
        f'Mn_INk and DRV_EN go to page {DRIVERS_PAGE}.  All 20 GPIO are used.')


def decoder_block(sh, ox, oy):
    sh.frame(ox, oy, ox + 148, oy + 60, 'Encoder chip-select decoder and SSI bus')
    X, Y = ox + 40, oy + 34
    u = sh.part('U6', X, Y, ref=(1.5, -13.2, 'l'), val=(1.5, 15.3, 'l'))
    for pin, name in ((2, 'ENC_A0'), (3, 'ENC_A1')):
        x, y = u.p(pin)
        sh.wire((x, y), (x - 4, y))
        sh.glabel(name, x - 4, y, 180, 'input')
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    sh.power('+3V3', *r5.p(1))
    r6 = sh.part('R6', rx - 9, ry + 19, rot=90, **ACROSS)
    sh.wire(r6.p(1), (rx - 16, ry + 19))
    sh.glabel('ENC_DO_MCU', rx - 16, ry + 19, 180, 'output')
    sh.wire(r5.p(2), (rx, ry + 19))
    sh.wire(r6.p(2), (rx + 7, ry + 19))
    sh.glabel('ENC_DO', rx + 7, ry + 19, 0, 'bidirectional')
    sh.note(
        ox + 68, oy + 43,
        'Select (A1 A0): 00 = ENC1, 01 = ENC2, 10 = ENC3, 11 = ENC4.',
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        sh.wire((x - 16, oy + 31), (x - 14, oy + 31))
        sh.glabel(net_of(j.ref, 3), x - 14, oy + 31, 0, 'passive')
        sh.wire(r.p(1), (x - 16, oy + 40), (x - 14, oy + 40))
        sh.glabel('ENC_CLK', x - 14, oy + 40, 0, 'input')
        for pin in (4, 5):
            x, y = j.p(pin)
            name = net_of(j.ref, pin)
            sh.wire((x, y), (x - 4, y))
            sh.glabel(name, x - 4, y, 180, 'output' if name == 'ENC_DO' else 'input')
    sh.wire((xs[0] - 20, top), (xs[-1] - 4, top))
    sh.power('+3V3', xs[0] - 12, top)
    sh.wire((xs[0] - 20, bot), (xs[-1] - 20, bot))
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    sh.glabel('SCL', r2.x + 8, scl - 4, 0, 'bidirectional')
    # Qwiic 3V3 pin: only joined to +3V3 if the jumper is fitted
    sh.wire((ox + 28, v), (ox + 28, v + 4))
    sh.glabel('QWIIC_3V3', ox + 28, v + 4, 0, 'passive')
    jp = sh.part('JP1', ox + 54, v + 12, ref=(2.2, -0.2, 'l'), val=(2.2, 1.8, 'l'))
    sh.wire((ox + 46, v), (ox + 46, v + 12), jp.p(1))
    sh.wire(jp.p(2), (ox + 42, jp.p(2)[1]), (ox + 42, v + 10))
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    d3 = sh.part('D3', ox + 132, Y + 2, ref=(-1.5, -7.4, 'r'), val=(-1.5, -5.6, 'r'))
    x, y = d3.p(4)
    sh.wire((x, y), (x - 4, y))
    sh.glabel('LED_DATA', x - 4, y, 180, 'input')
    sh.nc(d3.p(2))
    x, y = d3.p(1)
    sh.wire((x, y), (x, y - 6))
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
